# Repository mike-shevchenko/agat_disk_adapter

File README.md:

# agat_disk_adapter
KiCad project for Agat/Apple2 140K FDD connector PCB

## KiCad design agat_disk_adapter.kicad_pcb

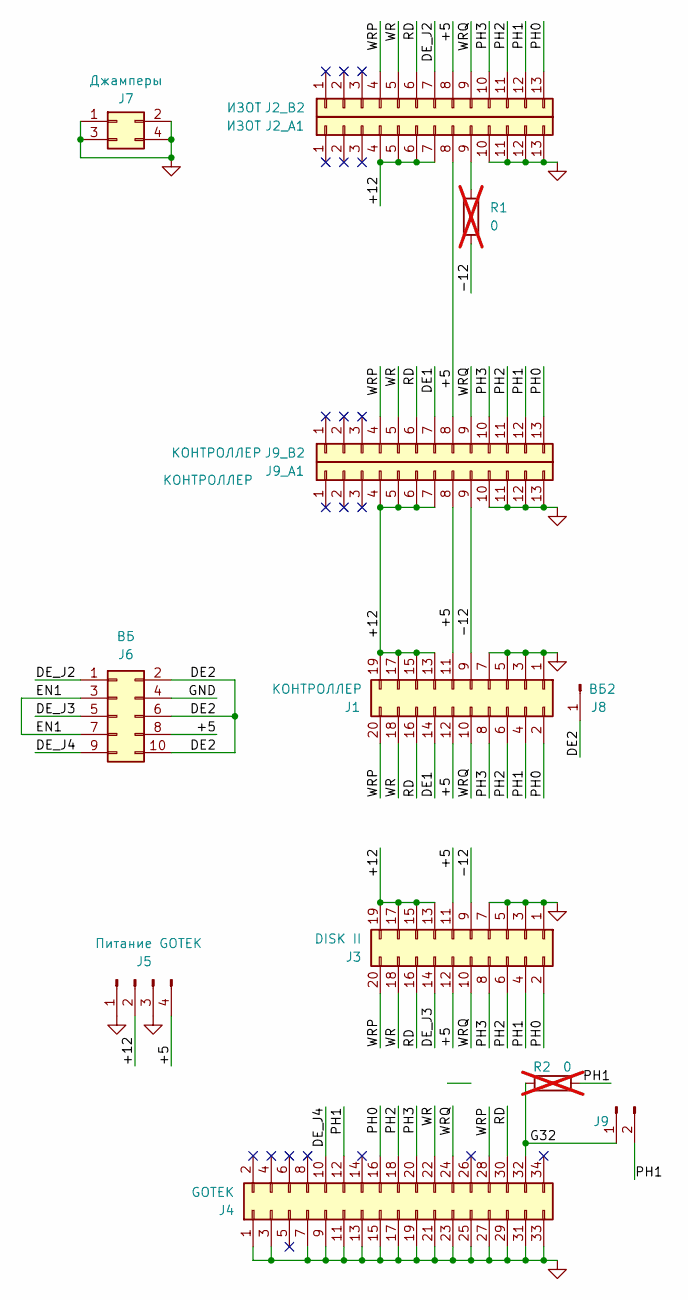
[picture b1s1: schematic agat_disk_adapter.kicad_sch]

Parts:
J1: КОНТРОЛЛЕР; IDC-Header_2x10_P2.54mm_Vertical
J2_A1, J2_B2: ИЗОТ; JST_EH_B13B-EH-A_1x13_P2.50mm_Vertical
J3: DISK II; IDC-Header_2x10_P2.54mm_Vertical
J4: GOTEK; IDC-Header_2x17_P2.54mm_Vertical
J5: Питание GOTEK; Molex_KK-254_AE-6410-04A_1x04_P2.54mm_Vertical
J6: ВБ; IDC-Header_2x05_P2.54mm_Vertical
J7: Джамперы; PinHeader_2x02_P2.54mm_Vertical
J8: ВБ2; PinHeader_1x01_P2.54mm_Horizontal
J9: PIN_32; PinHeader_1x02_P2.54mm_Horizontal
J9_A1, J9_B2: КОНТРОЛЛЕР; JST_EH_B13B-EH-A_1x13_P2.50mm_Vertical
R1, R2: 0; R_1206_3216Metric; not fitted

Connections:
/+5: J1.11, J1.12, J2_A1.8, J2_B2.8, J3.11, J3.12, J5.4, J6.8, J9_A1.8, J9_B2.8
/+12: J1.13, J1.15, J1.17, J1.19, J2_A1.4, J2_A1.5, J2_A1.6, J2_A1.7, J3.13, J3.15, J3.17, J3.19, J5.2, J9_A1.4, J9_A1.5, J9_A1.6, J9_A1.7
/-12: J1.9, J3.9, J9_A1.9, R1.2
/DE1: J1.14, J9_B2.7
/DE2: J6.2, J6.6, J6.10, J8.1 (Pin_1_1)
/DE_J2: J2_B2.7, J6.1
/DE_J3: J3.14, J6.5
/DE_J4: J4.10, J6.9
/EN1: J6.3, J6.7
/G32: J4.32, J9.1, R2.2
/PH0: J1.2, J2_B2.13, J3.2, J4.16, J9_B2.13
/PH1: J1.4, J2_B2.12, J3.4, J4.12, J9.2, J9_B2.12, R2.1
/PH2: J1.6, J2_B2.11, J3.6, J4.18, J9_B2.11
/PH3: J1.8, J2_B2.10, J3.8, J4.20, J9_B2.10
/RD: J1.16, J2_B2.6, J3.16, J4.30, J9_B2.6
/WR: J1.18, J2_B2.5, J3.18, J4.22, J9_B2.5
/WRP: J1.20, J2_B2.4, J3.20, J4.28, J9_B2.4
/WRQ: J1.10, J2_B2.9, J3.10, J4.24, J9_B2.9
GND: J1.1, J1.3, J1.5, J1.7, J2_A1.10, J2_A1.11, J2_A1.12, J2_A1.13, J3.1, J3.3, J3.5, J3.7, J4.1, J4.3, J4.7, J4.9, J4.11, J4.13, J4.15, J4.17, J4.19, J4.21, J4.23, J4.25, J4.27, J4.29, J4.31, J4.33, J5.1, J5.3, J6.4, J7.1, J7.2, J7.3, J7.4, J9_A1.10, J9_A1.11, J9_A1.12, J9_A1.13
unnamed: J2_A1.9, R1.1

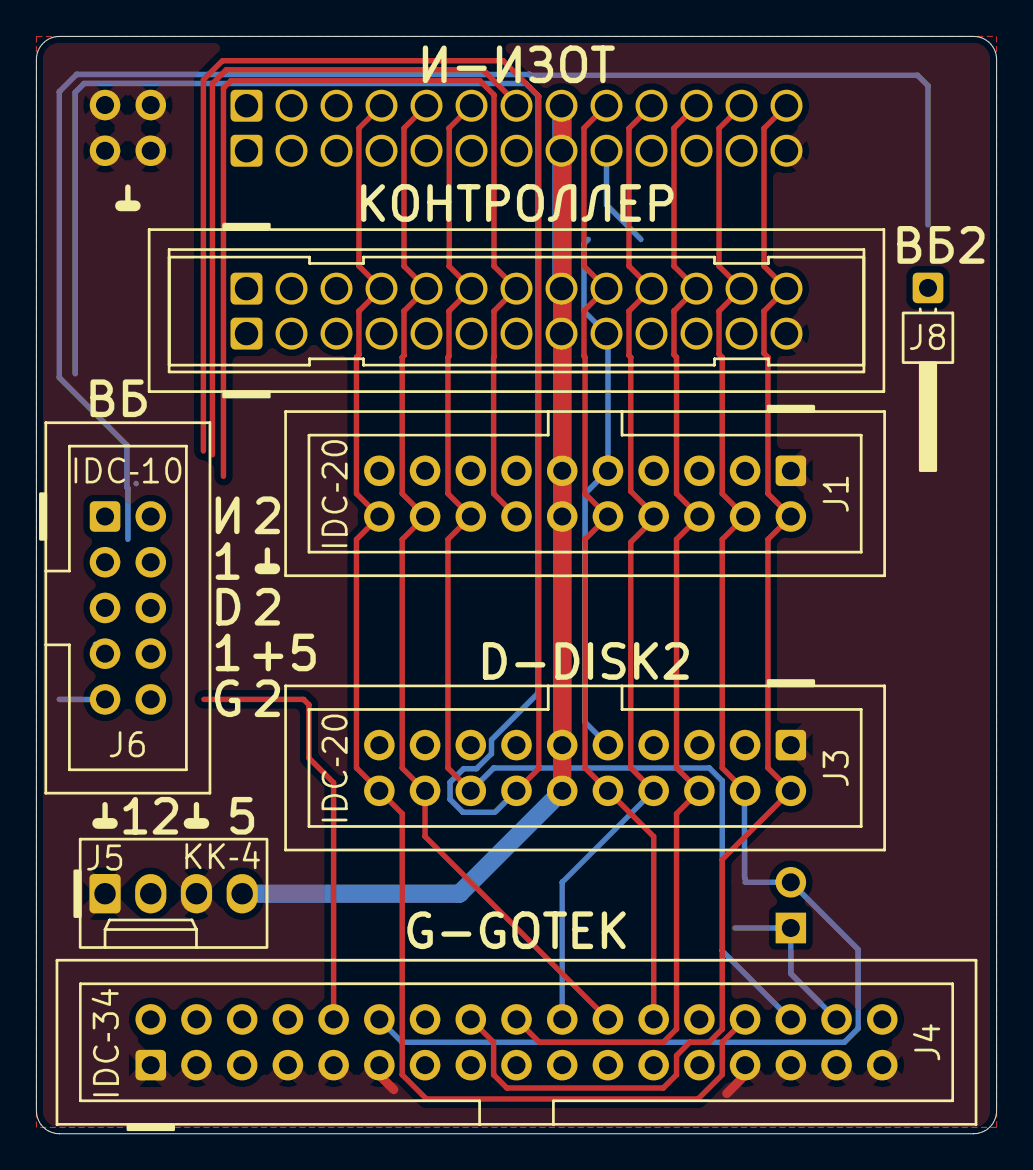
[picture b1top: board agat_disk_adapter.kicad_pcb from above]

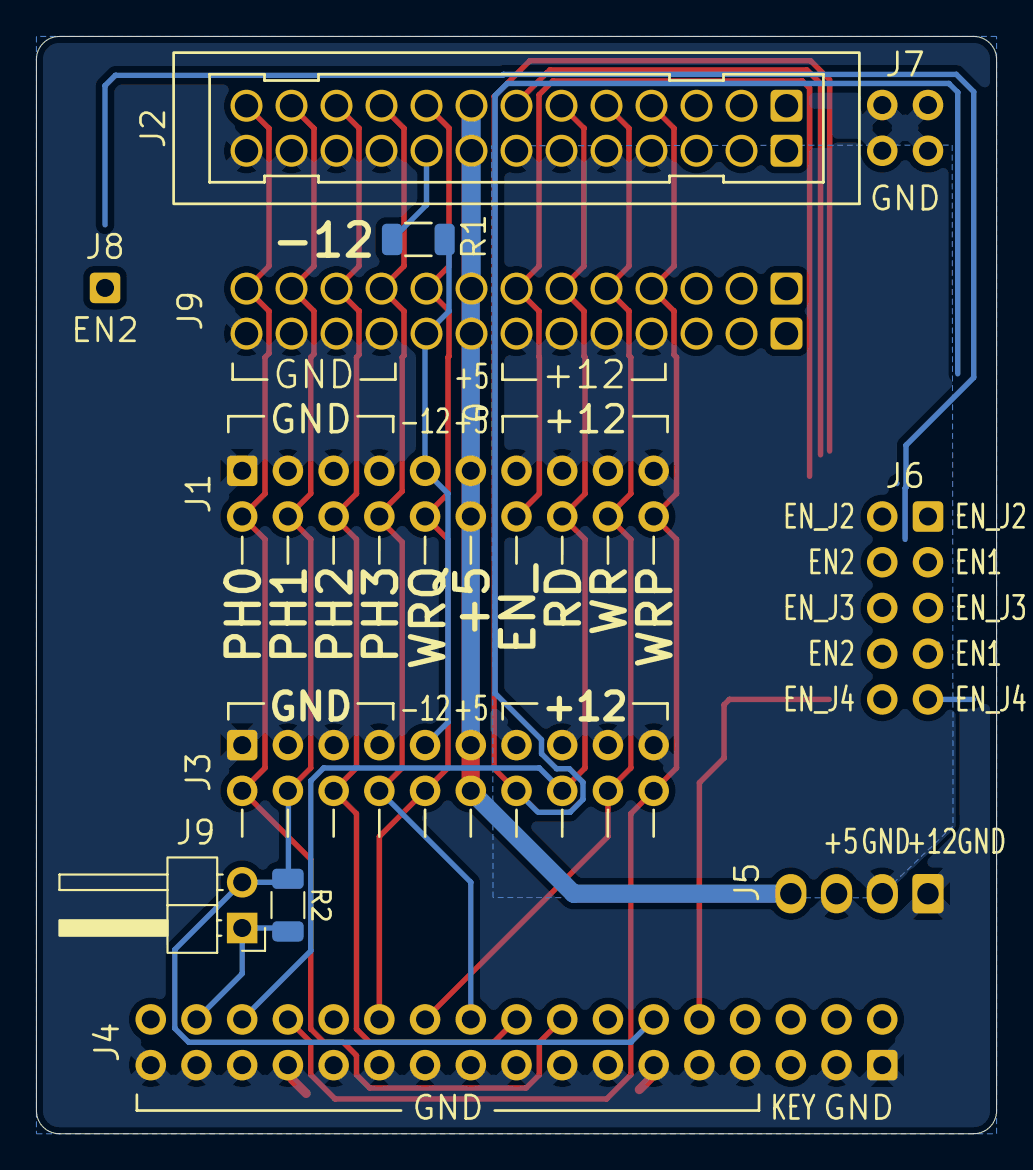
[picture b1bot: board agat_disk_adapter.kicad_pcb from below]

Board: 2 copper layers, 53.3 x 61.0 mm, 14 parts (5 on the bottom side), 20 nets.
